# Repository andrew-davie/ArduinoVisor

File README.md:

# ArduinoVisor

Project/source files for Arduino Mechanical TV
Using ATMEGA32U4 processor (Arduino Micro)

For build log and instructions, see
https://www.taswegian.com/NBTV/forum/viewforum.php?f=28

Files are setup for Visual Studio Code project with PlatformIO installed.
Authors: Andrew Davie, Keith Colson

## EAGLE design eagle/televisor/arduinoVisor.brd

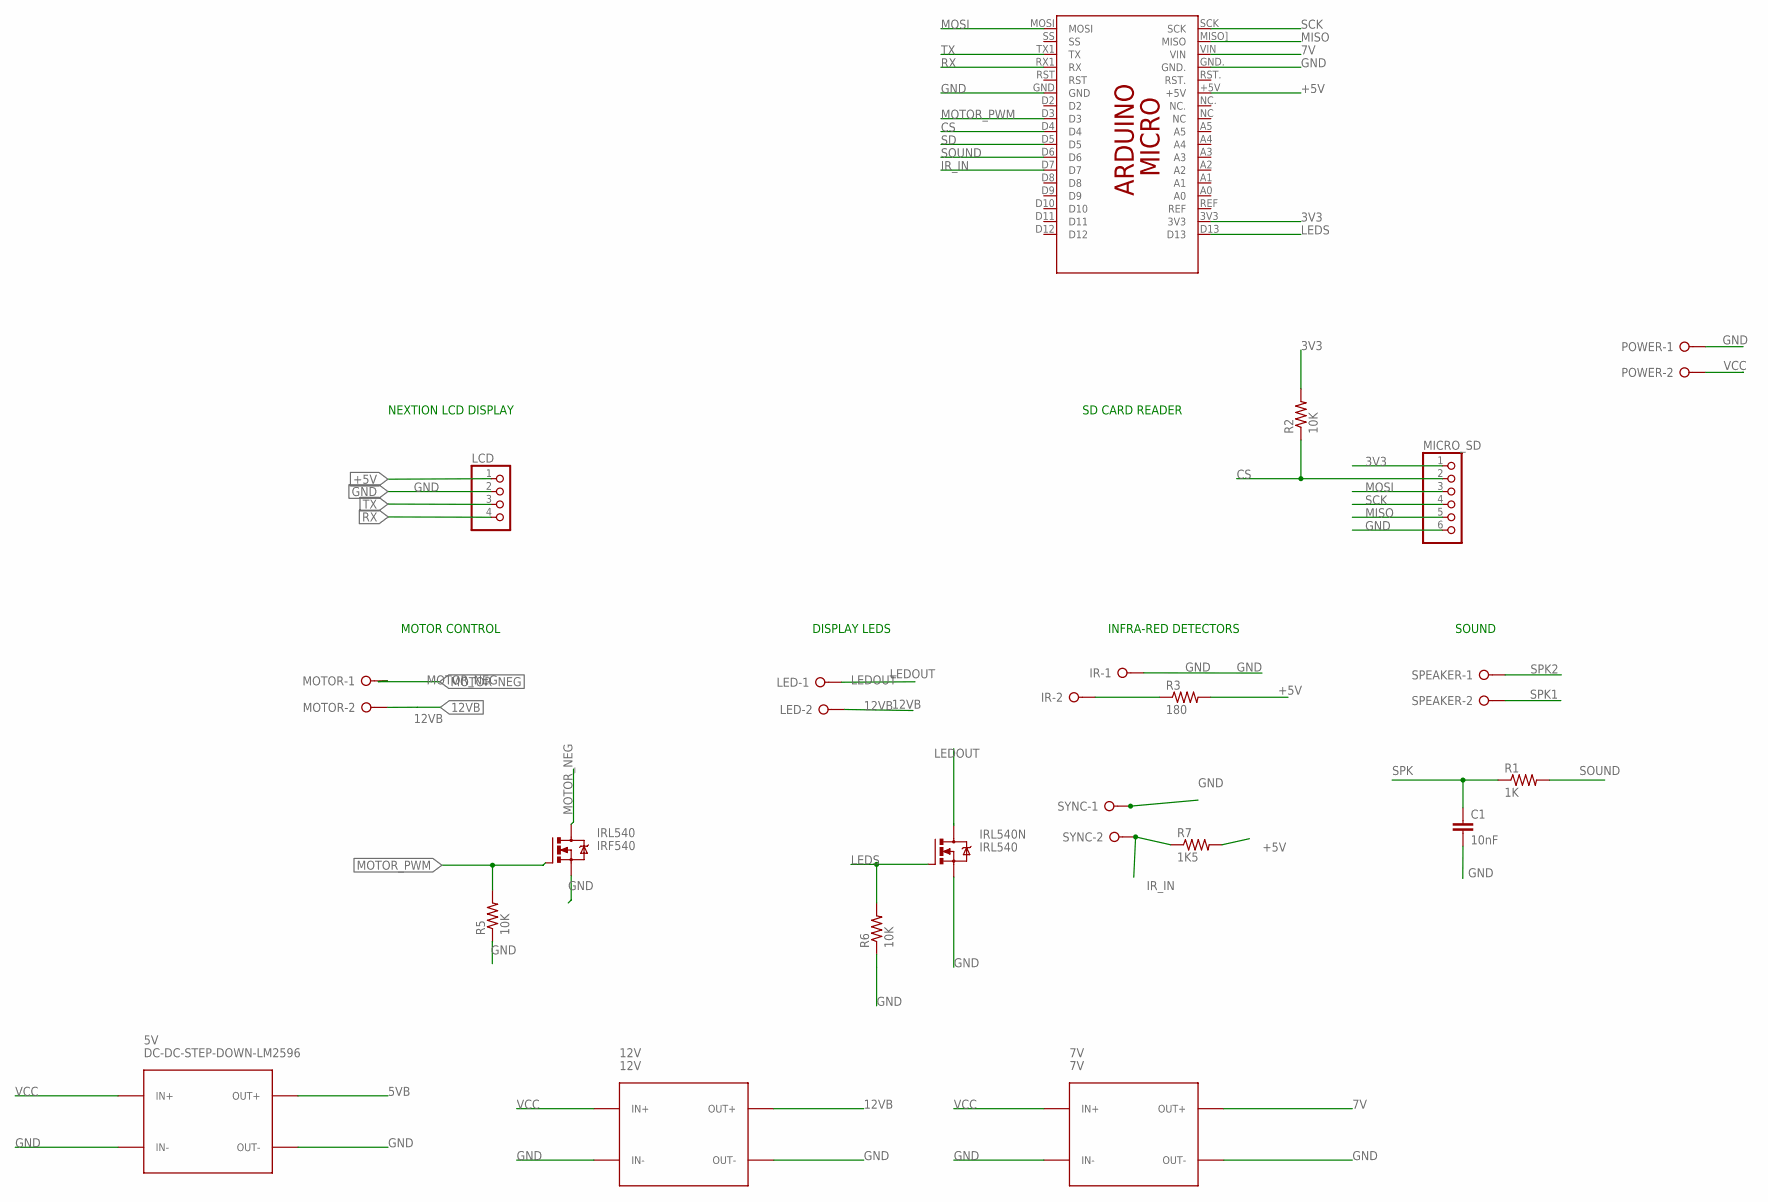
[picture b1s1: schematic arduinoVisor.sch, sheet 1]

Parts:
5V: DC-DC-STEP-DOWN-LM2596
7V: 7V; DC-DC-STEP-DOWN-LM2596
12V: 12V; DC-DC-STEP-DOWN-LM2596
C1: 10nF; C2.5-2
IR: W237-02P; W237-132
IRL540: IRF540; TO220BV
IRL540N: IRL540; TO220BV
LCD: PINHD-1X4; 1X04
LED: W237-02P; W237-132
MICRO_SD: PINHD-1X6; 1X06
MOTOR: W237-02P; W237-132
PCB2: ARDUINO_MICRO
POWER: W237-02P; W237-132
R1: 1K; 0207/10
R2, R5, R6: 10K; 0207/10
R3: 180; 0207/10
R7: 1K5; 0207/10
SPEAKER: W237-02P; W237-132
SYNC: W237-02P; W237-132

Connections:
3V3: MICRO_SD.1, PCB2.3V3, R2.2
5VB: 5V.OUT+; also elsewhere on the board
7V: 7V.OUT+, PCB2.VIN
12VB: 12V.OUT+, LED.2, MOTOR.2
+5V: LCD.1, PCB2.+5V, R3.2, R7.2
CS: MICRO_SD.2, PCB2.D4, R2.1
GND: 5V.IN-, 5V.OUT-, 7V.IN-, 7V.OUT-, 12V.IN-, 12V.OUT-, C1.2, IR.1, IRL540.S, IRL540N.S, LCD.2, MICRO_SD.6, PCB2.GND, PCB2.GND., POWER.1, R5.1, R6.1, SYNC.1; also elsewhere on the board
IR_IN: PCB2.D7, R7.1, SYNC.2
IR_OUT: IR.2, R3.1
LEDOUT: IRL540N.D, LED.1
LEDS: IRL540N.G, PCB2.D13, R6.2
MISO: MICRO_SD.5, PCB2.MISO] (MISO)
MOSI: MICRO_SD.3, PCB2.MOSI
MOTOR_NEG: IRL540.D, MOTOR.1
MOTOR_PWM: IRL540.G, PCB2.D3, R5.2
RX: LCD.4, PCB2.RX1 (RX)
SCK: MICRO_SD.4, PCB2.SCK
SD: PCB2.D5; also elsewhere on the board
SOUND: PCB2.D6, R1.2
SPK: C1.1, R1.1; also elsewhere on the board
SPK1: SPEAKER.2; also elsewhere on the board
SPK2: SPEAKER.1; also elsewhere on the board
TX: LCD.3, PCB2.TX1 (TX)
VCC: 5V.IN+, 7V.IN+, 12V.IN+, POWER.2

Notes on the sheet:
MOTOR CONTROL
DISPLAY LEDS
INFRA-RED DETECTORS
NEXTION LCD DISPLAY
SD CARD READER
SOUND

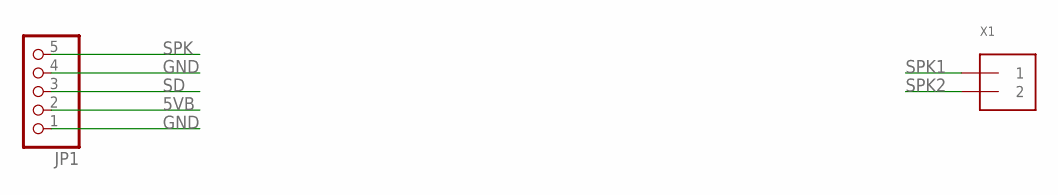
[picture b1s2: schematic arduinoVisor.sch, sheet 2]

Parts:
JP1: HEADER-1X570MIL; 1X05_ROUND_70
X1: TERMBLOCK_1X2; TERMBLOCK_1X2-3.5MM

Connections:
5VB: JP1.2; also elsewhere on the board
GND: JP1.1, JP1.4; also elsewhere on the board
SD: JP1.3; also elsewhere on the board
SPK: JP1.5; also elsewhere on the board
SPK1: X1.1; also elsewhere on the board
SPK2: X1.2; also elsewhere on the board

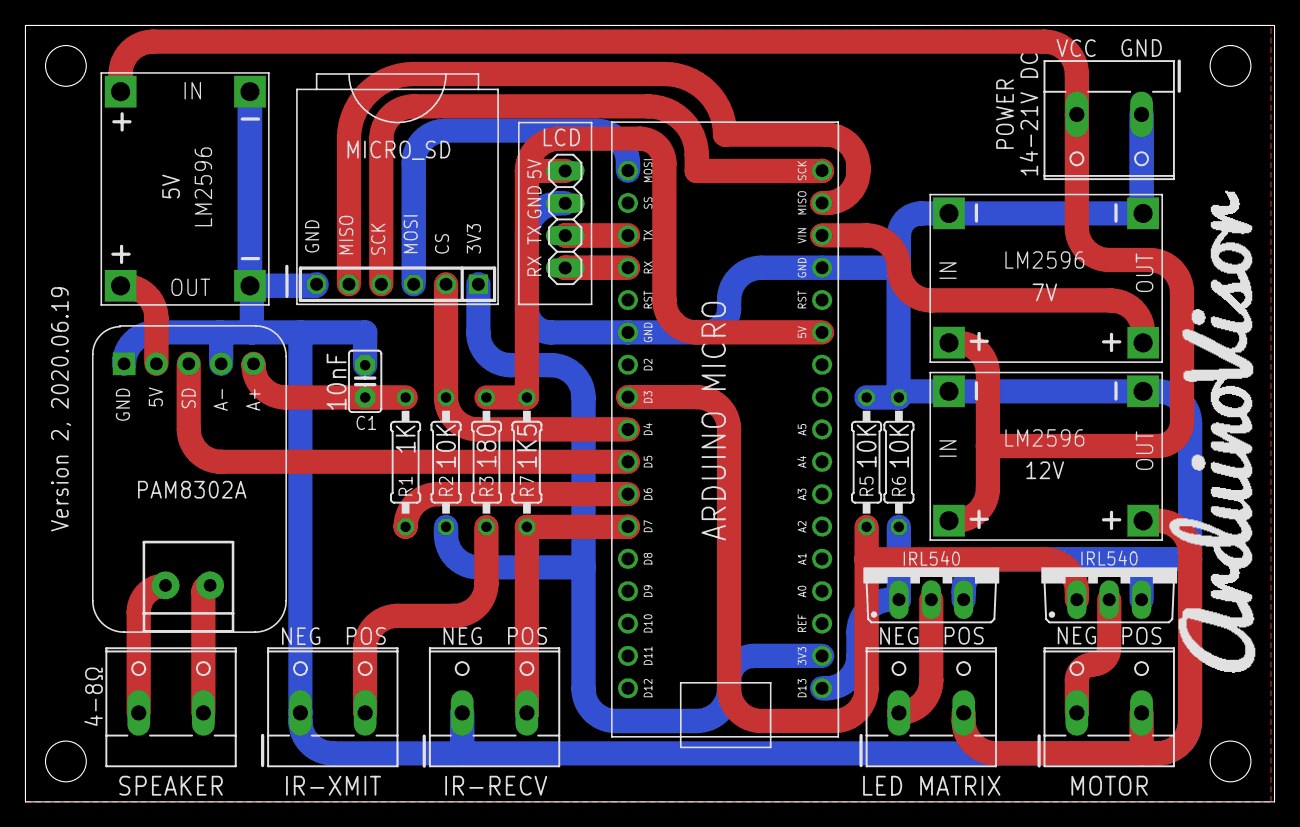
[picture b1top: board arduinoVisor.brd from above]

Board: 2 copper layers, 98.1 x 61.0 mm, 23 parts (0 on the bottom side), 24 nets.

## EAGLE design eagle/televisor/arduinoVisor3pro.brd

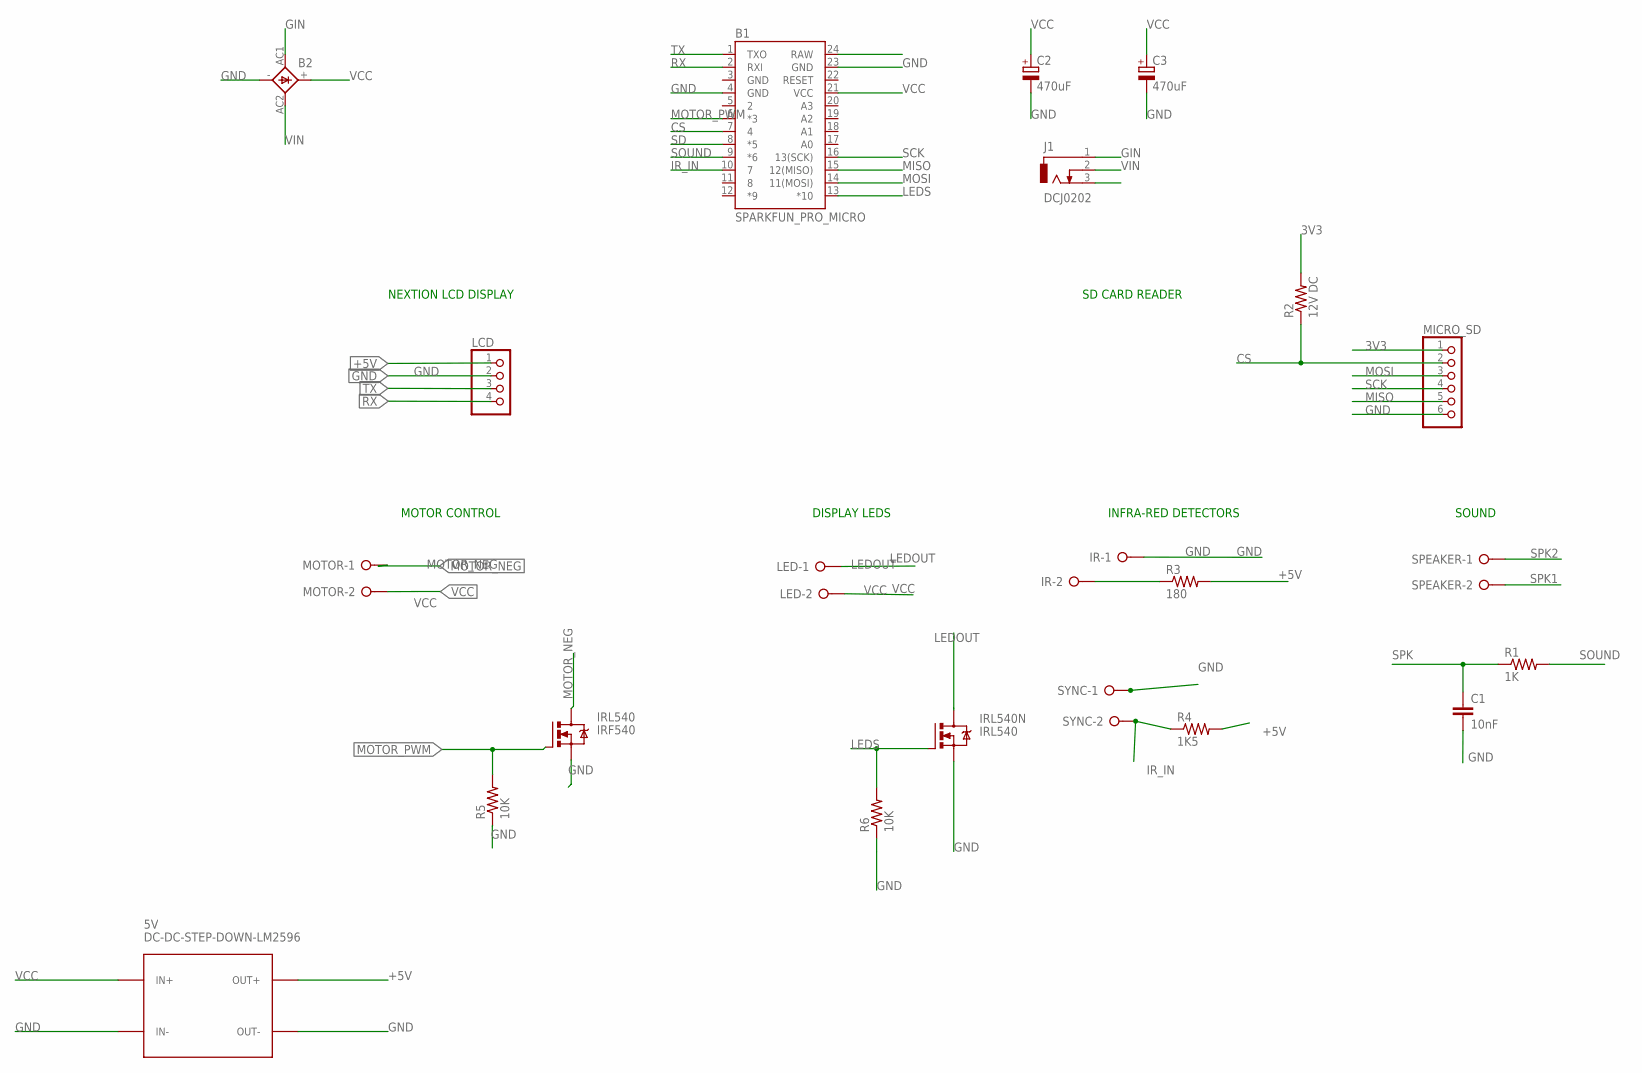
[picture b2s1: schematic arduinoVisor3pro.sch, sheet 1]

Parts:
5V: DC-DC-STEP-DOWN-LM2596
B1: SPARKFUN_PRO_MICRO
B2: 1KAB
C1: 10nF; C2.5-2
C2, C3: 470uF; E5-6
IR: W237-02P; W237-132
IRL540: IRF540; TO220BV
IRL540N: IRL540; TO220BV
J1: DCJ0202
LCD: PINHD-1X4; 1X04
LED: W237-02P; W237-132
MICRO_SD: PINHD-1X6; 1X06
MOTOR: W237-02P; W237-132
R1: 1K; 0207/10
R2: 12V DC; 0207/10
R3: 180; 0207/10
R4: 1K5; 0207/10
R5, R6: 10K; 0207/10
SPEAKER: W237-02P; W237-132
SYNC: W237-02P; W237-132

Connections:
3V3: MICRO_SD.1, R2.2
+5V: 5V.OUT+, B1.24 (RAW), LCD.1, R3.2, R4.2; also elsewhere on the board
CS: B1.7 (4), MICRO_SD.2, R2.1
GIN: B2.AC1, J1.1
GND: 5V.IN-, 5V.OUT-, B1.3 (GND), B1.4 (GND), B1.23 (GND), B2.-, C1.2, C2.-, C3.-, IR.1, IRL540.S, IRL540N.S, LCD.2, MICRO_SD.6, R5.1, R6.1, SYNC.1; also elsewhere on the board
IR_IN: B1.10 (7), R4.1, SYNC.2
IR_OUT: IR.2, R3.1
LEDOUT: IRL540N.D, LED.1
LEDS: B1.13 (*10), IRL540N.G, R6.2
MISO: B1.15 (12(MISO)), MICRO_SD.5
MOSI: B1.14 (11(MOSI)), MICRO_SD.3
MOTOR_NEG: IRL540.D, MOTOR.1
MOTOR_PWM: B1.6 (*3), IRL540.G, R5.2
RX: B1.2 (RXI), LCD.4
SCK: B1.16 (13(SCK)), MICRO_SD.4
SD: B1.8 (*5); also elsewhere on the board
SOUND: B1.9 (*6), R1.2
SPK: C1.1, R1.1; also elsewhere on the board
SPK1: SPEAKER.2; also elsewhere on the board
SPK2: SPEAKER.1; also elsewhere on the board
TX: B1.1 (TXO), LCD.3
VCC: 5V.IN+, B1.21 (VCC), B2.+, C2.+, C3.+, LED.2, MOTOR.2
VIN: B2.AC2, J1.2

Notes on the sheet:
MOTOR CONTROL
DISPLAY LEDS
INFRA-RED DETECTORS
NEXTION LCD DISPLAY
SD CARD READER
SOUND

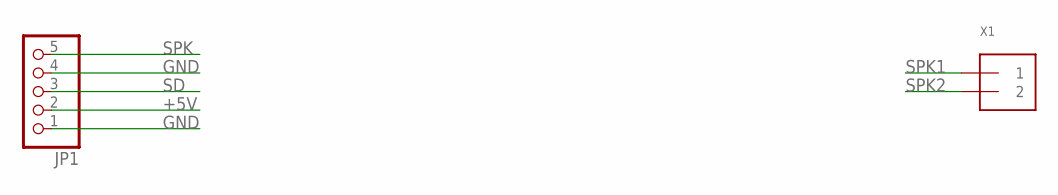
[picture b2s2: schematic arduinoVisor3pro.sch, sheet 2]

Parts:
JP1: HEADER-1X570MIL; 1X05_ROUND_70
X1: TERMBLOCK_1X2; TERMBLOCK_1X2-3.5MM

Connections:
+5V: JP1.2; also elsewhere on the board
GND: JP1.1, JP1.4; also elsewhere on the board
SD: JP1.3; also elsewhere on the board
SPK: JP1.5; also elsewhere on the board
SPK1: X1.1; also elsewhere on the board
SPK2: X1.2; also elsewhere on the board

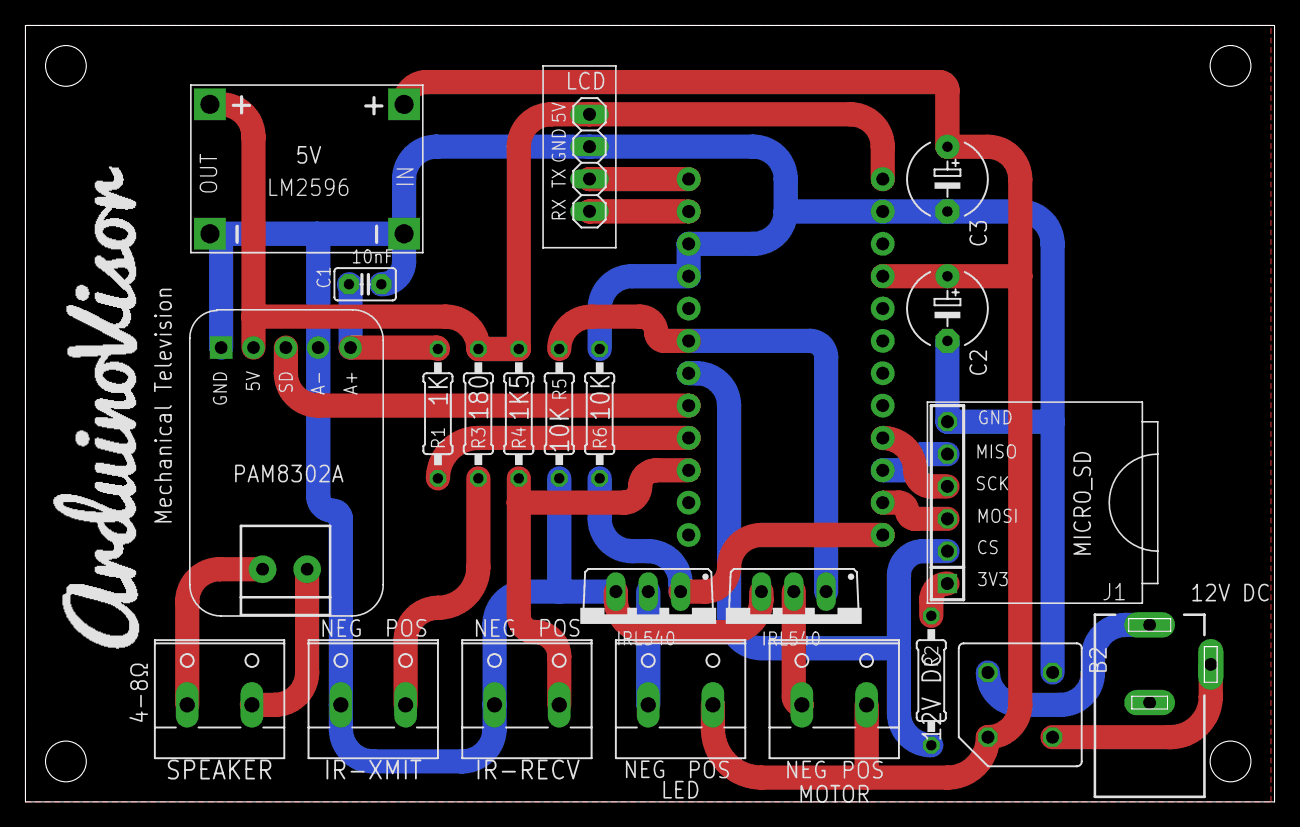
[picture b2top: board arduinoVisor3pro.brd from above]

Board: 2 copper layers, 98.1 x 61.0 mm, 24 parts (0 on the bottom side), 23 nets.

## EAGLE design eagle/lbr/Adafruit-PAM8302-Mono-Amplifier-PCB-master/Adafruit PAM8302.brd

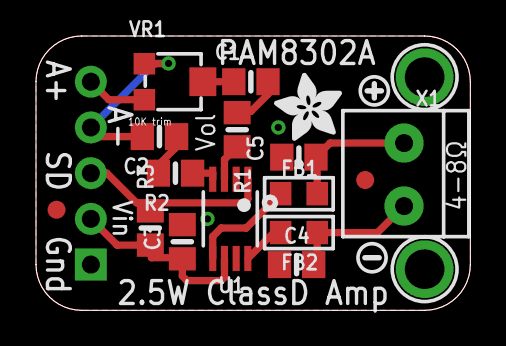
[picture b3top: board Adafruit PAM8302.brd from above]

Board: 2 copper layers, 24.1 x 15.2 mm, 22 parts (1 on the bottom side), 14 nets.

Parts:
C1, C2: 1uF; 0805-NO
C3: 10uF; 0805-NO
C4, C5: 220pF; 0805-NO
FB1, FB2: Ferrite; _0805
FID1, FID2: FIDUCIAL""; FIDUCIAL_1MM
JP1: 1X05_ROUND_70
R1, R2: 100; 0805-NO
R3: 10K; 0805-NO
U1: PAM8302AASCR; MSOP8_0.65MM
U$3: SYMBOL_PLUS
U$4: SYMBOL_MINUS
U$5: ADAFRUIT_3.5MM
U$6: PCBFEAT-REV-040
U$10, U$11: MOUNTINGHOLE2.0; MOUNTINGHOLE_2.0_PLATED
VR1: 10K trim; TRIMPOT_BOURNS_3303W
X1: TERMBLOCK_1X2-3.5MM

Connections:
AIN+: JP1.5, VR1.3
AIN-: C2.2, JP1.4, VR1.1
GND: C3.2, C4.2, C5.2, JP1.1, U1.7
unnamed: R2.2, U1.4
unnamed: R1.2, U1.3
unnamed: C1.1, R1.1
unnamed: C2.1, R2.1
unnamed: FB2.1, U1.8
unnamed: FB1.1, U1.5
unnamed: C1.2, VR1.2
SD: JP1.3, R3.2, U1.1
VCC: C3.1, JP1.2, R3.1, U1.6
VO+: C5.1, FB1.2, X1.1
VO-: C4.1, FB2.2, X1.2

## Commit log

2020-06-16 updated to KC version 16 + convert to VC
2020-06-16 setup
2020-06-16 updated .gitignore
2020-06-16 test
2020-06-16 fixed test
2020-06-16 added eagle board files and libraries Use these to make your own arduinovisor boards
2020-06-16 Added NBTV8-format WAV files. Put these on your MicroSD card plugged into the ArduinoVisor
2020-06-16 cleaned up reported errors in schematic, board prelude to rejigging power to KC version
2020-06-17 Added Nextion build files
2020-06-17 ignoring eagle build files
2020-06-17 failed. lets try again
2020-06-17 fixed to ignore transient eagle files
2020-06-17 fixed 'repeat' and no-display autoplay
2020-06-18 board IR swap pins. ground planes. code uncrustified.
2020-07-20 revitalising

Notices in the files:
parts and their libraries:
microbuilder: This work is placed in the public domain, and may be freely used for commercial and non-commercial work with the following conditions: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
diy-modules boo: Released under the Creative Commons Attribution 4.0 International License: http://creativecommons.org/licenses/by/4.0
